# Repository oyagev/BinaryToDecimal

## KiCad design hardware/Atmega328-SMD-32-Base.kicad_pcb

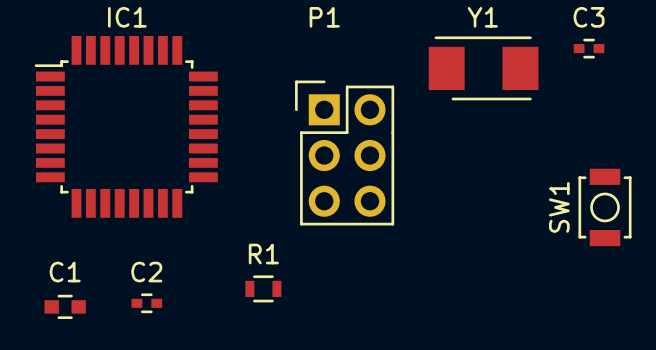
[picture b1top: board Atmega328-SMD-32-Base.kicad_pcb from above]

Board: 2 copper layers, 8 parts (0 on the bottom side), 8 nets, no tracks yet.

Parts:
C1: 100nF; C_0603
C2, C3: 22pF; C_0402
IC1: ATMEGA328P-A; TQFP-32_7x7mm_Pitch0.8mm
P1: CONN_02X03; Pin_Header_Straight_2x03
R1: 10K; R_0603
SW1: SW_PUSH; SW_SPST_B3U-1000P
Y1: Crystal; Crystal_SMD_5032_2Pads

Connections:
+5V: C1.1, IC1.4, IC1.6, IC1.18, P1.2, R1.1
/MISO: IC1.16, P1.1
/MOSI: IC1.15, P1.4
/SCK: IC1.17, P1.3
/XTAL1: C2.1, IC1.7, Y1.1
/XTAL2: C3.1, IC1.8, Y1.2
/reset: IC1.29, P1.5, R1.2, SW1.2
GND: C1.2, C2.2, C3.2, IC1.3, IC1.5, IC1.21, P1.6, SW1.1

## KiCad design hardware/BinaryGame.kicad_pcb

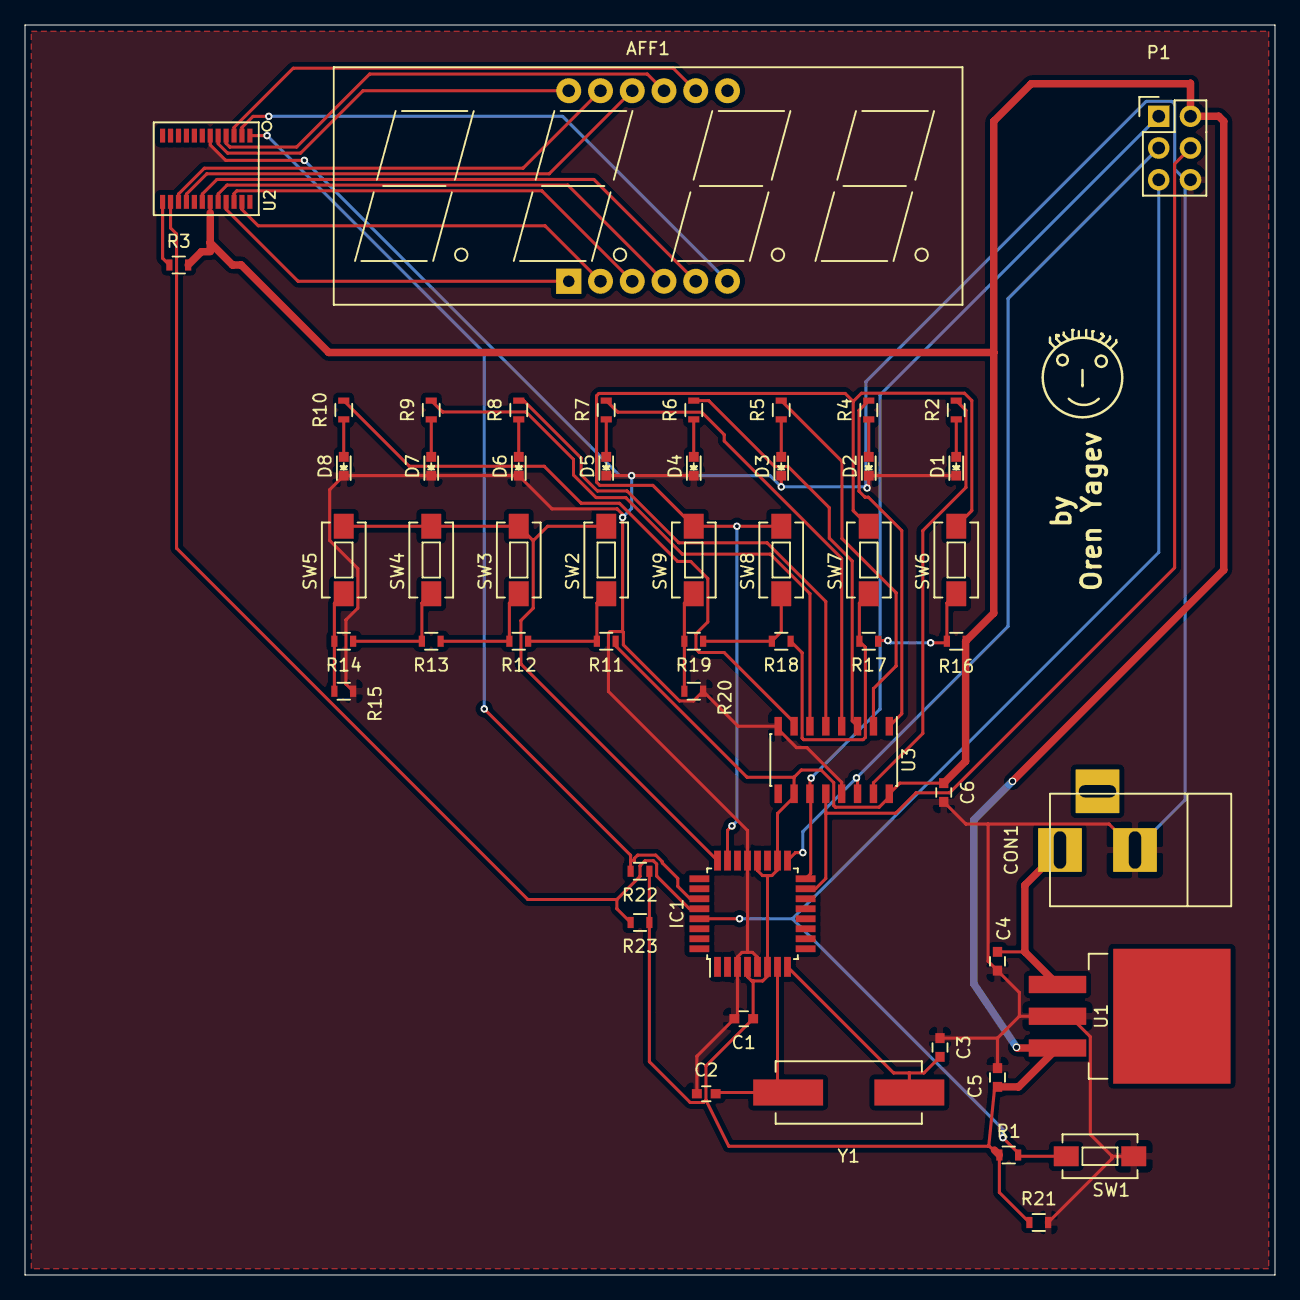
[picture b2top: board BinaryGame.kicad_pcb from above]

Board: 2 copper layers, 100.0 x 100.0 mm, 54 parts (0 on the bottom side), 49 nets.

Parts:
AFF1: LTC-5723HR; Cx56-12
C1, C5, C6: 0.1uF; C_0603
C2, C3: 22pF; C_0603
C4: 0.33uF; C_0603
CON1: BARREL_JACK
D1, D2, D3, D4, D5, D6, D7, D8: ILED1; LED_0603
IC1: ATMEGA328-AU; TQFP-32_7x7mm_Pitch0.8mm
P1: CONN_02X03; Pin_Header_Straight_2x03
R1, R21, R22, R23: 10K; R_0603
R2, R4, R5, R6, R7, R8, R9, R10: 150; R_0603
R3: 23.2K; R_0603
R11, R12, R13, R14, R15, R16, R17, R18, R19, R20: 3K3; R_0603
SW1: SW_PUSH; SW_SPST_EVQPE1
SW2: Ind5; SW_SPST_EVQPE1
SW3: Ind6; SW_SPST_EVQPE1
SW4: Ind7; SW_SPST_EVQPE1
SW5: Ind8; SW_SPST_EVQPE1
SW6: Ind1; SW_SPST_EVQPE1
SW7: Ind2; SW_SPST_EVQPE1
SW8: Ind3; SW_SPST_EVQPE1
SW9: Ind4; SW_SPST_EVQPE1
U1: TO-263-3Lead
U2: AS1115; QSOP-24
U3: 74HC595; SOIC-16_3.9x9.9mm_Pitch1.27mm
Y1: 16MHz; Crystal_HC49-SD_SMD

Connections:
+5V: C1.1, C5.1, C6.1, IC1.4, IC1.6, IC1.18, IC1.20, P1.2, R1.1, R3.2, R11.1, R16.1, R21.1, R22.1, R23.1, U1.3, U2.19, U3.10, U3.16
/Atmega328-SMD-32-Base/A0: IC1.23, SW6.2, SW7.2, SW8.2, SW9.2
/Atmega328-SMD-32-Base/A1: IC1.24, SW2.2, SW3.2, SW4.2, SW5.2
/Atmega328-SMD-32-Base/XTAL1: C2.2, IC1.7, Y1.2
/Atmega328-SMD-32-Base/XTAL2: C3.2, IC1.8, Y1.1
/Atmega328-SMD-32-Base/reset: IC1.29, P1.5, R1.2, SW1.2
/MCU_D11: IC1.15, P1.4, U3.12
/MCU_D12: IC1.16, P1.1, U3.11
/MCU_D13: IC1.17, P1.3, U3.14
/Power5V/Vin: C4.1, CON1.1, U1.1
/SCL: IC1.28, R23.2, U2.14
/SDA: IC1.27, R22.2, U2.1
GND: C1.2, C2.1, C3.1, C4.2, C5.2, C6.2, CON1.2, D1.1, D2.1, D3.1, D4.1, D5.1, D6.1, D7.1, D8.1, IC1.3, IC1.5, IC1.21, P1.6, R15.2, R20.2, R21.2, SW1.1, U1.2, U2.6, U3.8, U3.13
unnamed: AFF1.1, U2.21
unnamed: AFF1.2, U2.23
unnamed: AFF1.3, U2.22
unnamed: AFF1.4, U2.20
unnamed: AFF1.5, U2.18
unnamed: AFF1.6, U2.2
unnamed: AFF1.8, U2.3
unnamed: AFF1.9, U2.4
unnamed: AFF1.10, U2.16
unnamed: AFF1.11, U2.15
unnamed: AFF1.12, U2.5
unnamed: D1.2, R2.1
unnamed: D2.2, R4.1
unnamed: D3.2, R5.1
unnamed: D4.2, R6.1
unnamed: D5.2, R7.1
unnamed: D6.2, R8.1
unnamed: D7.2, R9.1
unnamed: D8.2, R10.1
unnamed: R2.2, U3.15
unnamed: R3.1, U2.13
unnamed: R4.2, U3.1
unnamed: R5.2, U3.2
unnamed: R6.2, U3.3
unnamed: R7.2, U3.4
unnamed: R8.2, U3.5
unnamed: R9.2, U3.6
unnamed: R10.2, U3.7
unnamed: R11.2, R12.1, SW2.1
unnamed: R12.2, R13.1, SW3.1
unnamed: R13.2, R14.1, SW4.1
unnamed: R14.2, R15.1, SW5.1
unnamed: R16.2, R17.1, SW6.1
unnamed: R17.2, R18.1, SW7.1
unnamed: R18.2, R19.1, SW8.1
unnamed: R19.2, R20.1, SW9.1
